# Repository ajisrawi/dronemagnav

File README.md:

# DroneMagNav — magnetic-anomaly navigation board for drones

GNSS-denied positioning from the Earth's crustal magnetic field, plus a
phone-operated great-circle route planner.

```
  LIS3MDL magnetometer ─┐                          ┌─ WDMAM anomaly map (SD)
  BMI088 IMU ───────────┼─ ESP32-S3 ─ particle ────┤  WMM core field model
  BMP280 baro ──────────┘   filter    matching     └─ Tolles-Lawson compensation
        │                        │
   u-blox GNSS (init/truth)      ├─ MAVLink GPS_INPUT → flight controller
                                 └─ WiFi AP → phone: offline map, route, upload
```

## Deliverables

| Item | Where | Status |
|---|---|---|
| Schematics (5 sheets) | `hardware/dronemagnav/*.kicad_sch`, `dronemagnav-schematic.pdf` | ERC 0 errors (1 intended warning) |
| PCB 64 × 60 mm, 4-layer, 30.5 mm Pixhawk hole pattern | `hardware/dronemagnav/dronemagnav.kicad_pcb` | routed, 0 unconnected, 0 electrical DRC |
| Fab package | `hardware/dronemagnav/fab/` (Gerber ZIP, drill, pick-and-place) | ready to upload |
| BOM | `docs/BOM.csv` | 28 line items, 56 parts, MPNs |
| Firmware (ESP32-S3, PlatformIO) | `firmware/`, images in `firmware/release/` | compiles with 0 warnings (Arduino-ESP32 3.3.11); WMM core-field model validated 100/100 against NOAA test vectors (0.001 nT) |
| Phone UI | `firmware/sdcard/www/index.html` | offline map, tap-to-route, upload |
| SD-card preparation | `tools/prepare_sd.py` | WDMAM v2 (1.5 GB text) → 51.9 MB binary grid, verified by `tools/wdmam_check.py`; WMM, coastline |
| Design document | `DroneMagNav-Design-Document.pdf` | study, diagrams, PCB, BOM, verification |

## Hardware
| Block | Part | Why |
|---|---|---|
| MCU / radio | ESP32-S3-WROOM-1-N16R8 | WiFi AP for the phone page, BLE, native USB, 8 MB PSRAM for map tiles + particle filter |
| Magnetometer | LIS3MDL (SPI) | 16-bit, ~40 nT after averaging; RM3100 upgrade via mast connector J5 |
| IMU | BMI088 (SPI) | drone-grade accel + gyro, vibration-robust |
| Barometer | BMP280 (SPI) | altitude for the field model |
| GNSS | u-blox MAX-M10S + U.FL | initialisation and truth reference |
| Storage | microSD (SDMMC 4-bit) | world anomaly map, WMM, coastline, web page |
| Interfaces | USB-C, JST-GH TELEM (MAVLink, 5 V in), JST-GH sensor mast (I2C) | Pixhawk-standard |
| Power | USB/FC 5 V → AMS1117-3.3 (digital) + AP2112K-3.3 (sensors) | separate clean sensor rail |

## How it navigates
1. **Compensate** the scalar field for the drone's own magnetism (18-term
   Tolles-Lawson, fitted once in flight with GNSS).
2. **Predict** position with the flight controller's velocity (or IMU dead
   reckoning) in a 600-particle filter.
3. **Update** each particle against *WMM core field + WDMAM anomaly* at the
   particle's location; resample; output mean and 1-σ.
4. **Feed** the estimate to the autopilot as `GPS_INPUT` when GNSS is lost.

**Expectations, honestly:** the WDMAM world grid is 3 arc-min (~5 km) and
upward-continued to 5 km, so with it alone you get drift-free
*kilometre-class* positioning — right for oceanic/jammed cruise, not landing.
Load a local aeromagnetic survey (`/maps/local.bin`, same format) for tens of
metres at drone altitude.

## Routing
The phone page shows an offline world coastline, you tap START and DEST, the
board computes the **great-circle** (shortest) path as evenly spaced waypoints
and uploads them to the flight controller as a MAVLink mission.

## Build / flash / prepare
See `firmware/README.md`. Short version: `pio run -t upload` over USB-C, then
`python tools/prepare_sd.py --wdmam <file> --wmm WMM.COF --coast <geojson>`
and copy `firmware/sdcard/*` to the card.

## Status / caveats
- Prototype; not certified for any regulated use.
- Firmware builds cleanly (PlatformIO, pioarduino platform, Arduino-ESP32
  core 3.3.11: 0 warnings, 1.08 MB flash of 4 MB app partition, 94 KB RAM).
  Ready-to-flash images are in `firmware/release/`. It has not yet run on
  real hardware, since the board has not been built.
- Vias in pads: 74 power vias were moved out of their pads into dog-bone
  stubs. Three remain where the routing leaves no room (BMI088 pads 2 and 4,
  microSD VDD pad) and must be filled and capped, see
  `hardware/dronemagnav/fab/FABRICATION-NOTES.md` (included in the Gerber ZIP).
- MAX-M10S straps checked against the u-blox integration manual
  (UBX-20053088 R05): `VIO_SEL` left open selects 3.3 V I/O, which is what the
  board supplies, so no change was needed. TIMEPULSE is tied inside the module
  to SAFEBOOT_N, so the firmware keeps GPIO16 input-only.
- Map data: WDMAM from the link you supplied; WMM.COF (NOAA) and Natural Earth
  coastline are free downloads you run through `prepare_sd.py`.

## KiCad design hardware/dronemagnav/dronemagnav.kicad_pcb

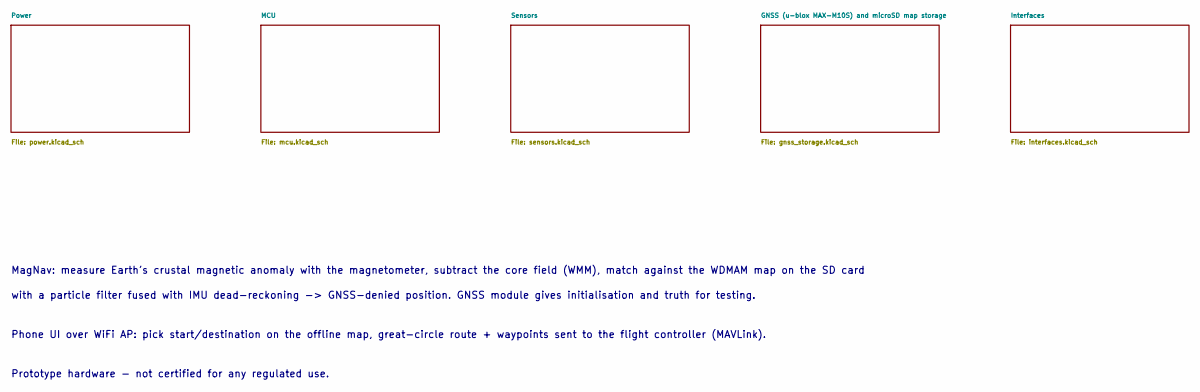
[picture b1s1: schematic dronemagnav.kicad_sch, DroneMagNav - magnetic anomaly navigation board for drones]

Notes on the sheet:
MagNav: measure Earth's crustal magnetic anomaly with the magnetometer, subtract the core field (WMM), match against the WDMAM map on the SD card
with a particle filter fused with IMU dead-reckoning -> GNSS-denied position. GNSS module gives initialisation and truth for testing.
Phone UI over WiFi AP: pick start/destination on the offline map, great-circle route + waypoints sent to the flight controller (MAVLink).
Prototype hardware - not certified for any regulated use.

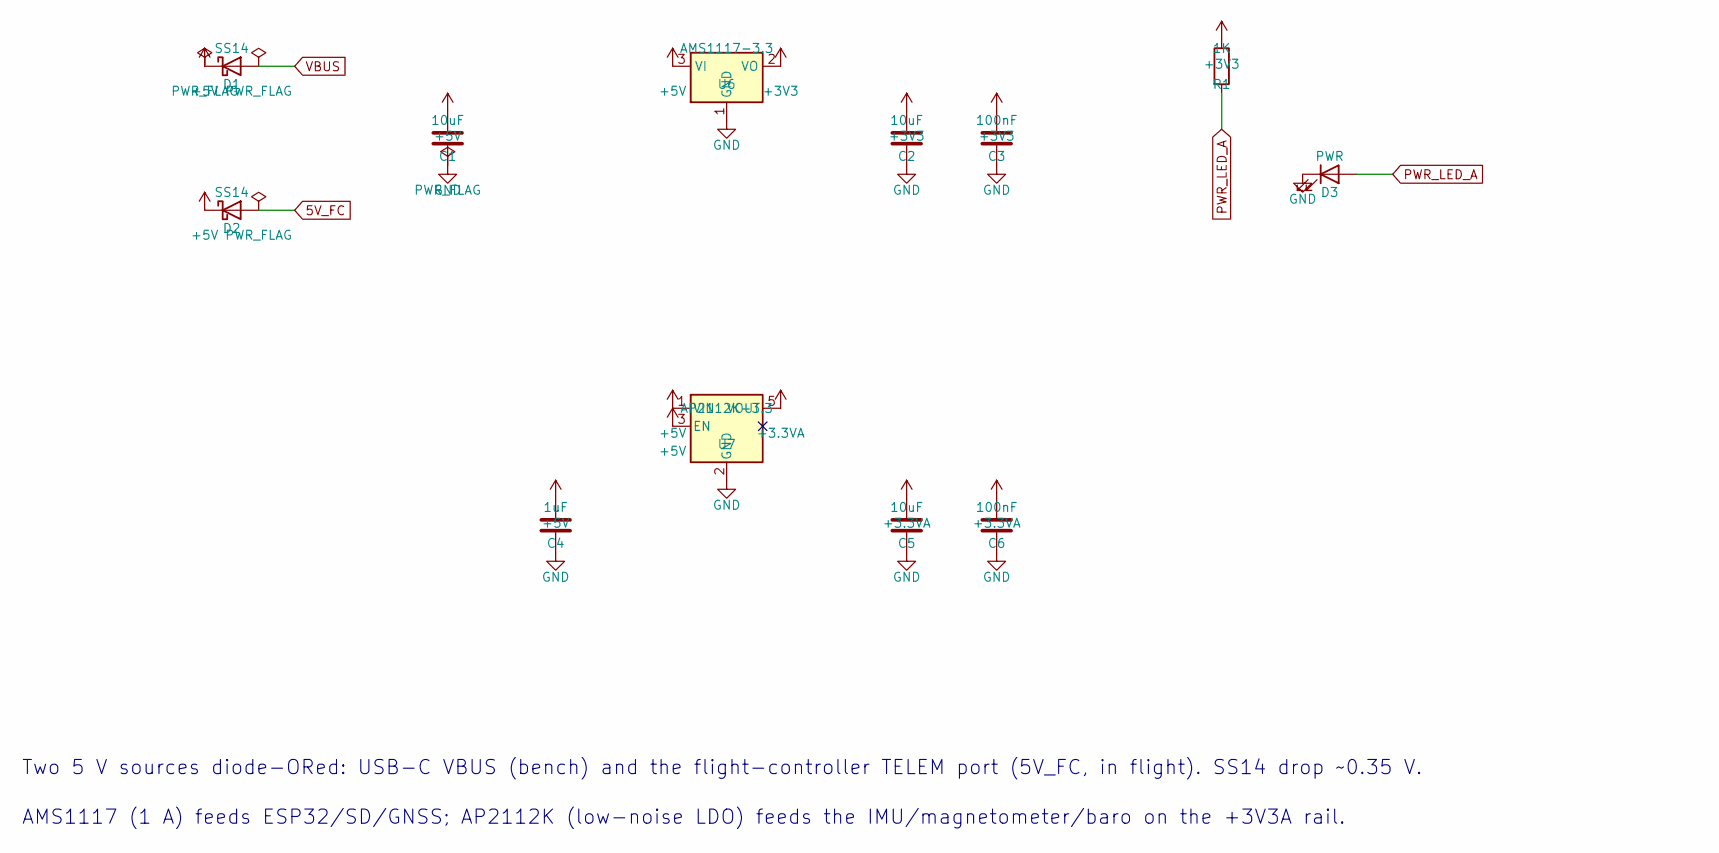
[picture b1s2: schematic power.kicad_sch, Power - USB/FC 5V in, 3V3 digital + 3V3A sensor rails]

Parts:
C1, C2, C5: 10uF; C_0805_2012Metric
C3, C6: 100nF; C_0603_1608Metric
C4: 1uF; C_0603_1608Metric
D1, D2: SS14; D_SMA
D3: PWR; LED_0603_1608Metric
R1: 1K; R_0603_1608Metric
U6: AMS1117-3.3; SOT-223-3_TabPin2
U7: AP2112K-3.3; SOT-23-5

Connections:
+3.3VA: C5.1, C6.1, U7.5 (VOUT); also elsewhere on the board
+3V3: C2.1, C3.1, R1.1, U6.2 (VO); also elsewhere on the board
PWR_LED_A: D3.2 (A), R1.2

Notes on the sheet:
Two 5 V sources diode-ORed: USB-C VBUS (bench) and the flight-controller TELEM port (5V_FC, in flight). SS14 drop ~0.35 V.
AMS1117 (1 A) feeds ESP32/SD/GNSS; AP2112K (low-noise LDO) feeds the IMU/magnetometer/baro on the +3V3A rail.

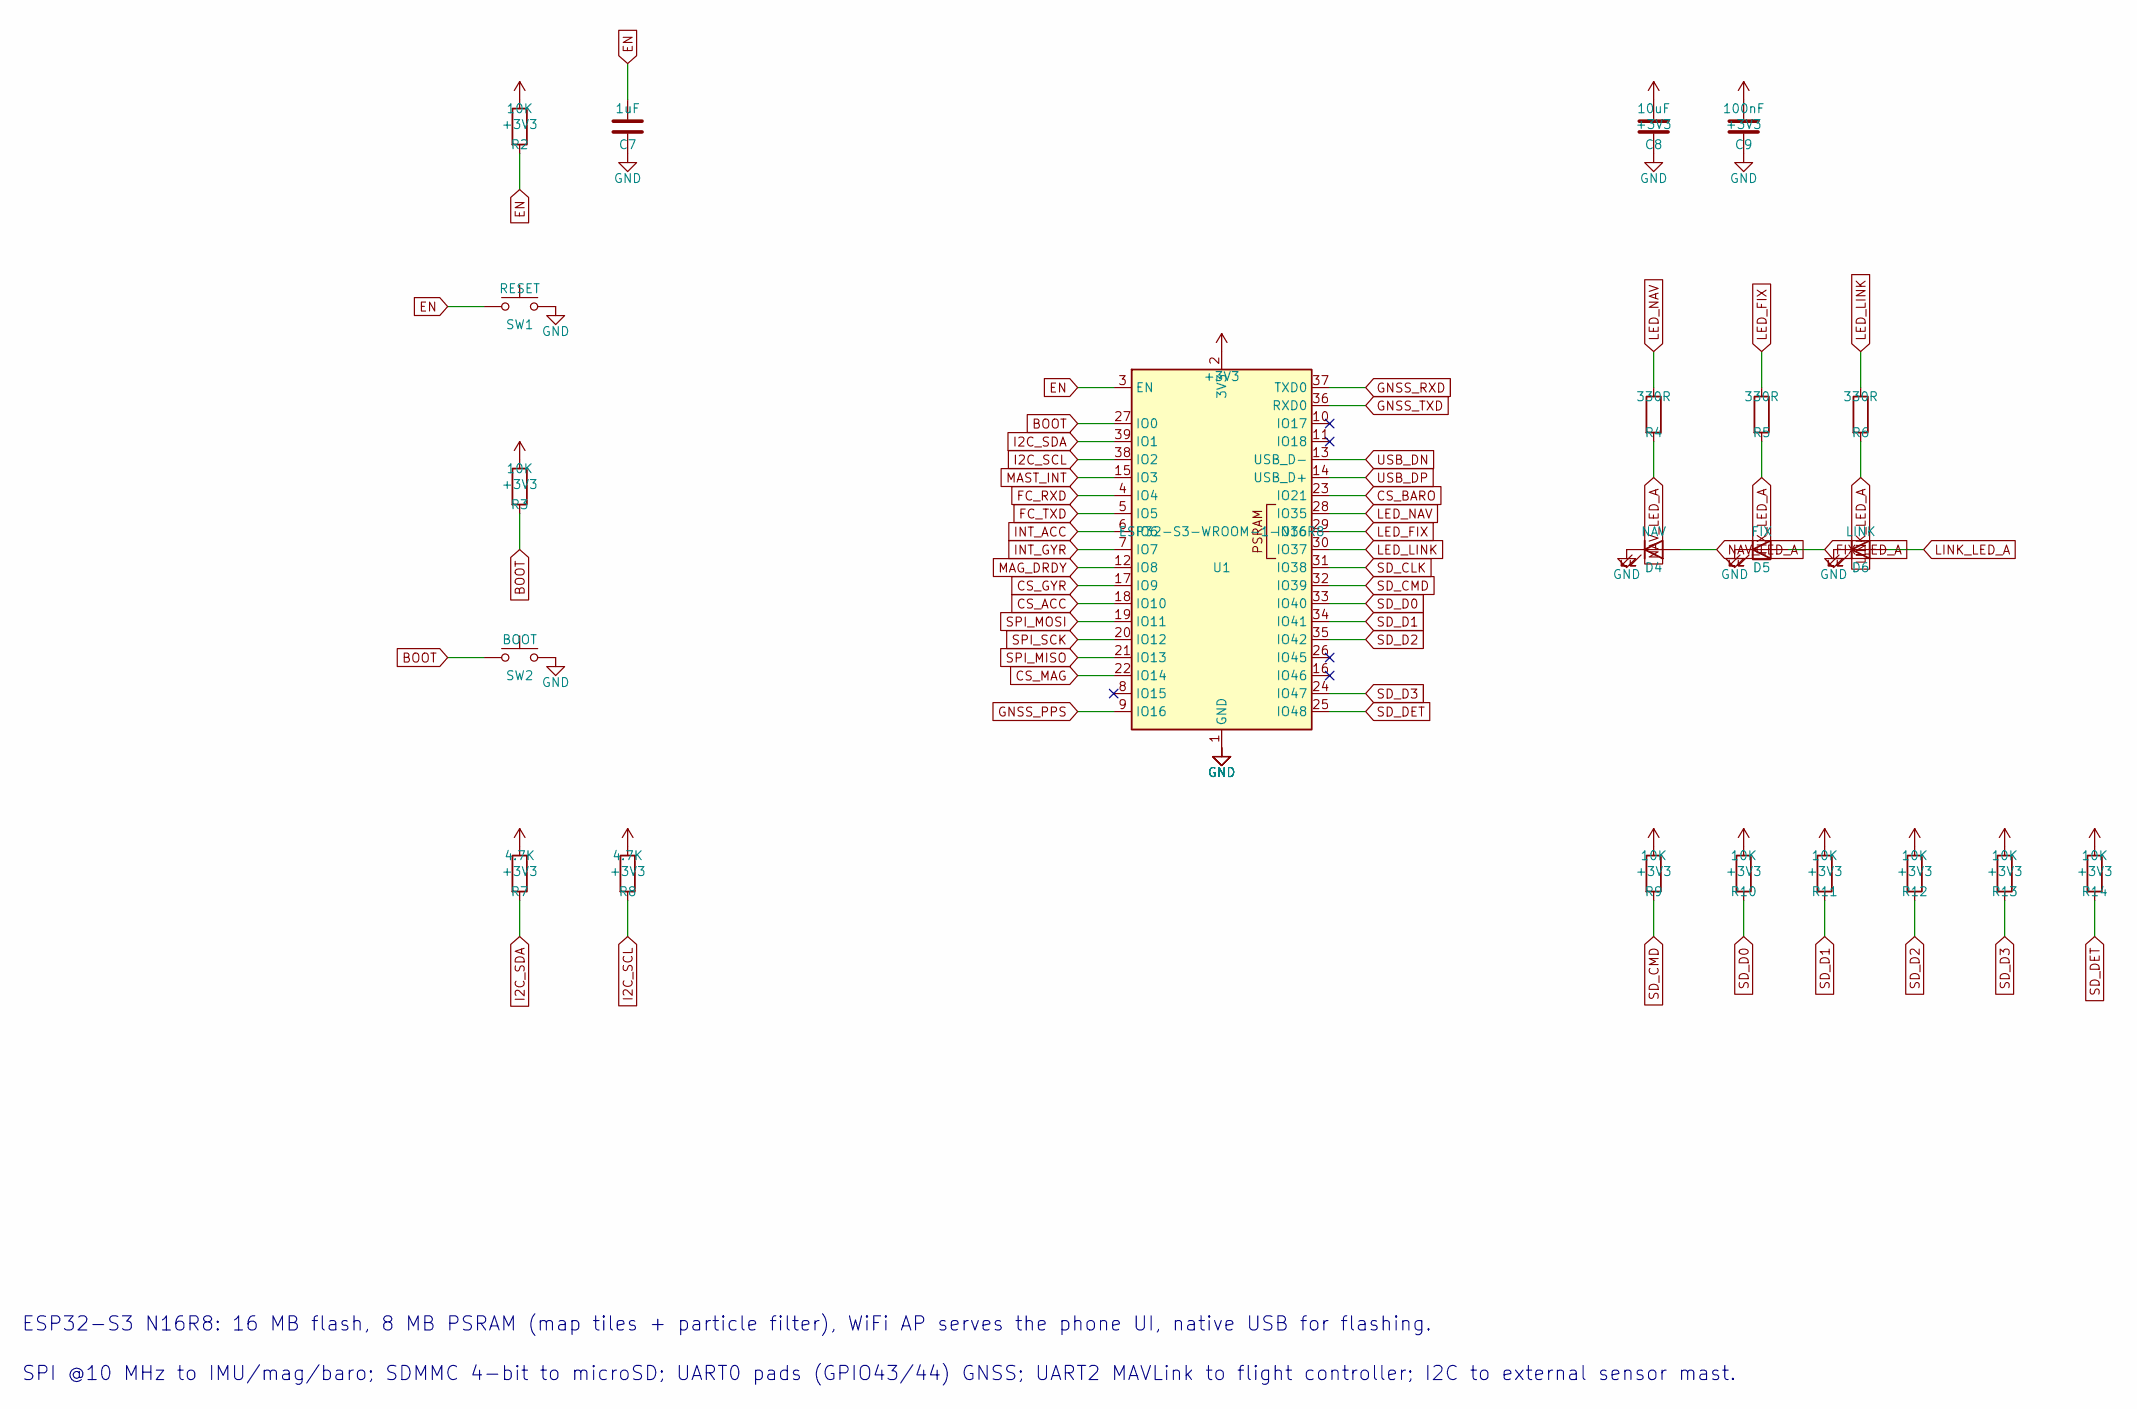
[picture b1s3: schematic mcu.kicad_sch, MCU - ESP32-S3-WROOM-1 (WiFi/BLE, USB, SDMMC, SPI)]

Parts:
C7: 1uF; C_0603_1608Metric
C8: 10uF; C_0805_2012Metric
C9: 100nF; C_0603_1608Metric
D4: NAV; LED_0603_1608Metric
D5: FIX; LED_0603_1608Metric
D6: LINK; LED_0603_1608Metric
R2, R3, R9, R10, R11, R12, R13, R14: 10K; R_0603_1608Metric
R4, R5, R6: 330R; R_0603_1608Metric
R7, R8: 4.7K; R_0603_1608Metric
SW1: RESET; SW_SPST_PTS645Sx43SMTR92
SW2: BOOT; SW_SPST_PTS645Sx43SMTR92
U1: ESP32-S3-WROOM-1-N16R8; ESP32-S3-WROOM-1

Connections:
+3V3: C8.1, C9.1, R2.1, R3.1, R7.1, R8.1, R9.1, R10.1, R11.1, R12.1, R13.1, R14.1, U1.2 (3V3); also elsewhere on the board
BOOT: R3.2, SW2.1, U1.27 (IO0)
CS_ACC: U1.18 (IO10); also elsewhere on the board
CS_BARO: U1.23 (IO21); also elsewhere on the board
CS_GYR: U1.17 (IO9); also elsewhere on the board
CS_MAG: U1.22 (IO14); also elsewhere on the board
EN: C7.1, R2.2, SW1.1, U1.3 (EN)
FC_RXD: U1.4 (IO4); also elsewhere on the board
FC_TXD: U1.5 (IO5); also elsewhere on the board
FIX_LED_A: D5.2 (A), R5.2
GNSS_PPS: U1.9 (IO16); also elsewhere on the board
GNSS_RXD: U1.37 (TXD0); also elsewhere on the board
GNSS_TXD: U1.36 (RXD0); also elsewhere on the board
I2C_SCL: R8.2, U1.38 (IO2); also elsewhere on the board
I2C_SDA: R7.2, U1.39 (IO1); also elsewhere on the board
INT_ACC: U1.6 (IO6); also elsewhere on the board
INT_GYR: U1.7 (IO7); also elsewhere on the board
LED_FIX: R5.1, U1.29 (IO36)
LED_LINK: R6.1, U1.30 (IO37)
LED_NAV: R4.1, U1.28 (IO35)
LINK_LED_A: D6.2 (A), R6.2
MAG_DRDY: U1.12 (IO8); also elsewhere on the board
MAST_INT: U1.15 (IO3); also elsewhere on the board
NAV_LED_A: D4.2 (A), R4.2
SD_CLK: U1.31 (IO38); also elsewhere on the board
SD_CMD: R9.2, U1.32 (IO39); also elsewhere on the board
SD_D0: R10.2, U1.33 (IO40); also elsewhere on the board
SD_D1: R11.2, U1.34 (IO41); also elsewhere on the board
SD_D2: R12.2, U1.35 (IO42); also elsewhere on the board
SD_D3: R13.2, U1.24 (IO47); also elsewhere on the board
SD_DET: R14.2, U1.25 (IO48); also elsewhere on the board
SPI_MISO: U1.21 (IO13); also elsewhere on the board
SPI_MOSI: U1.19 (IO11); also elsewhere on the board
SPI_SCK: U1.20 (IO12); also elsewhere on the board
USB_DN: U1.13 (USB_D-); also elsewhere on the board
USB_DP: U1.14 (USB_D+); also elsewhere on the board

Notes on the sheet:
ESP32-S3 N16R8: 16 MB flash, 8 MB PSRAM (map tiles + particle filter), WiFi AP serves the phone UI, native USB for flashing.
SPI @10 MHz to IMU/mag/baro; SDMMC 4-bit to microSD; UART0 pads (GPIO43/44) GNSS; UART2 MAVLink to flight controller; I2C to external sensor mast.

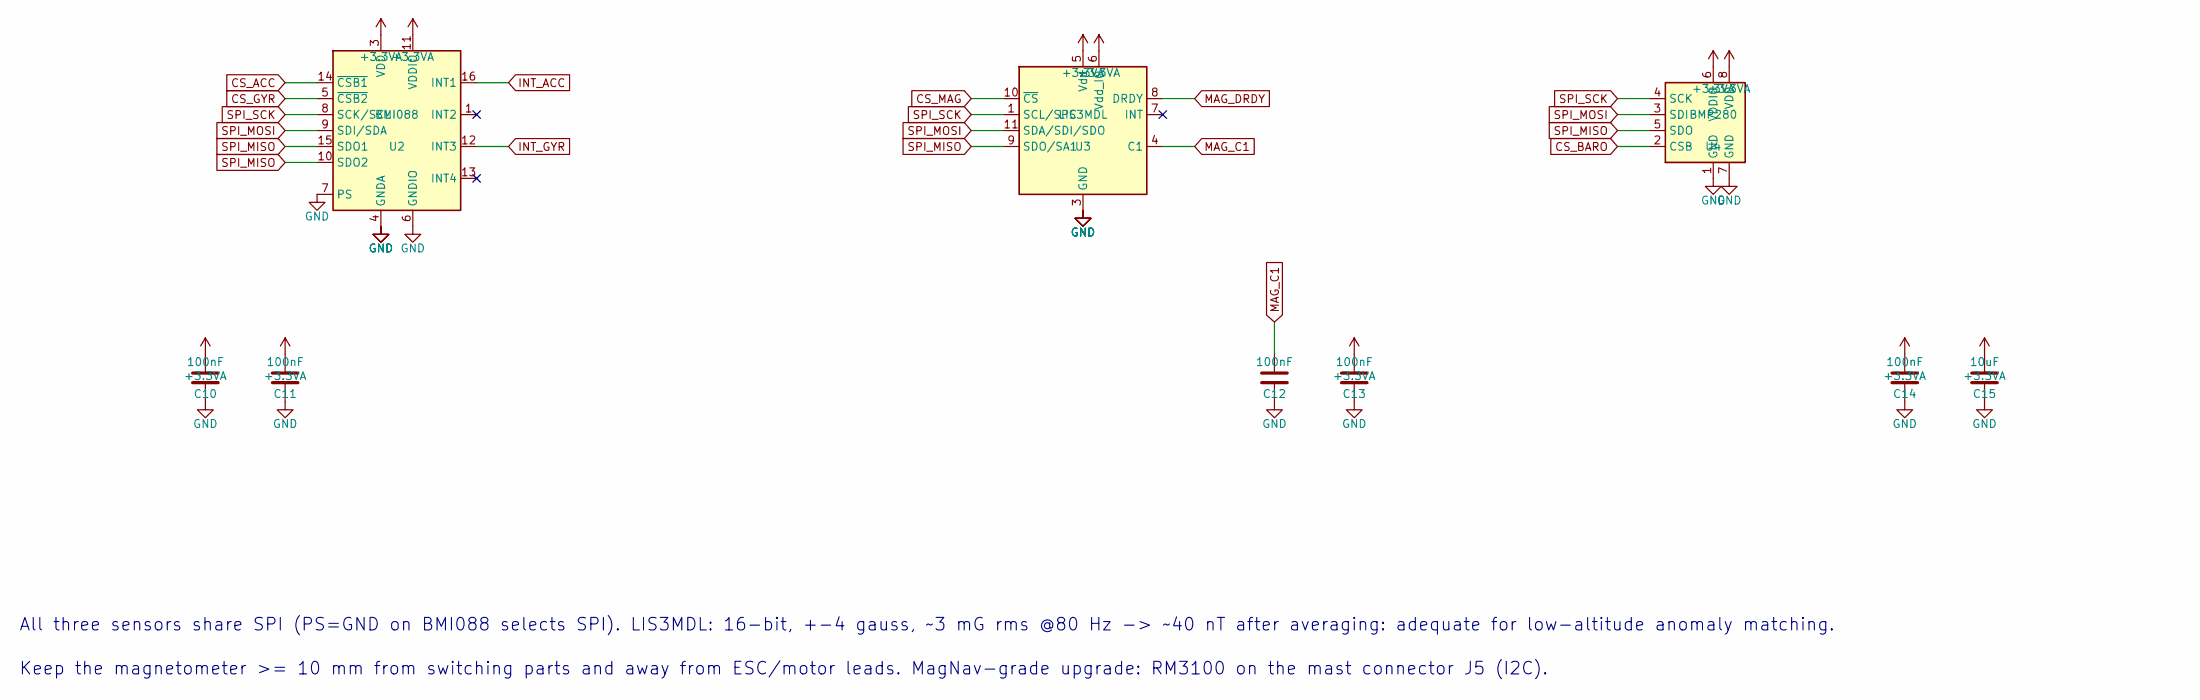
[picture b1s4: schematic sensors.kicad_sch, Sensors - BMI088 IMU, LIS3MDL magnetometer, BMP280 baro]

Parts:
C10, C11, C12, C13, C14: 100nF; C_0603_1608Metric
C15: 10uF; C_0805_2012Metric
U2: BMI088; Bosch_LGA-16_4.5x3mm_P0.5mm_LayoutBorder7x1y_ClockwisePinNu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
U3: LIS3MDL; LGA-12_2x2mm_P0.5mm
U4: BMP280; Bosch_LGA-8_2x2.5mm_P0.65mm_ClockwisePinNumbering

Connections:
+3.3VA: C10.1, C11.1, C13.1, C14.1, C15.1, U2.3 (VDD), U2.11 (VDDIO), U3.5 (Vdd), U3.6 (Vdd_IO), U4.6 (VDDIO), U4.8 (VDD); also elsewhere on the board
CS_ACC: U2.14 (~CSB1); also elsewhere on the board
CS_BARO: U4.2 (CSB); also elsewhere on the board
CS_GYR: U2.5 (~CSB2); also elsewhere on the board
CS_MAG: U3.10 (~CS); also elsewhere on the board
INT_ACC: U2.16 (INT1); also elsewhere on the board
INT_GYR: U2.12 (INT3); also elsewhere on the board
MAG_C1: C12.1, U3.4 (C1)
MAG_DRDY: U3.8 (DRDY); also elsewhere on the board
SPI_MISO: U2.10 (SDO2), U2.15 (SDO1), U3.9 (SDO/SA1), U4.5 (SDO); also elsewhere on the board
SPI_MOSI: U2.9 (SDI/SDA), U3.11 (SDA/SDI/SDO), U4.3 (SDI); also elsewhere on the board
SPI_SCK: U2.8 (SCK/SCL), U3.1 (SCL/SPC), U4.4 (SCK); also elsewhere on the board

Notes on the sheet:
All three sensors share SPI (PS=GND on BMI088 selects SPI). LIS3MDL: 16-bit, +-4 gauss, ~3 mG rms @80 Hz -> ~40 nT after averaging: adequate for low-altitude anomaly matching.
Keep the magnetometer >= 10 mm from switching parts and away from ESC/motor leads. MagNav-grade upgrade: RM3100 on the mast connector J5 (I2C).

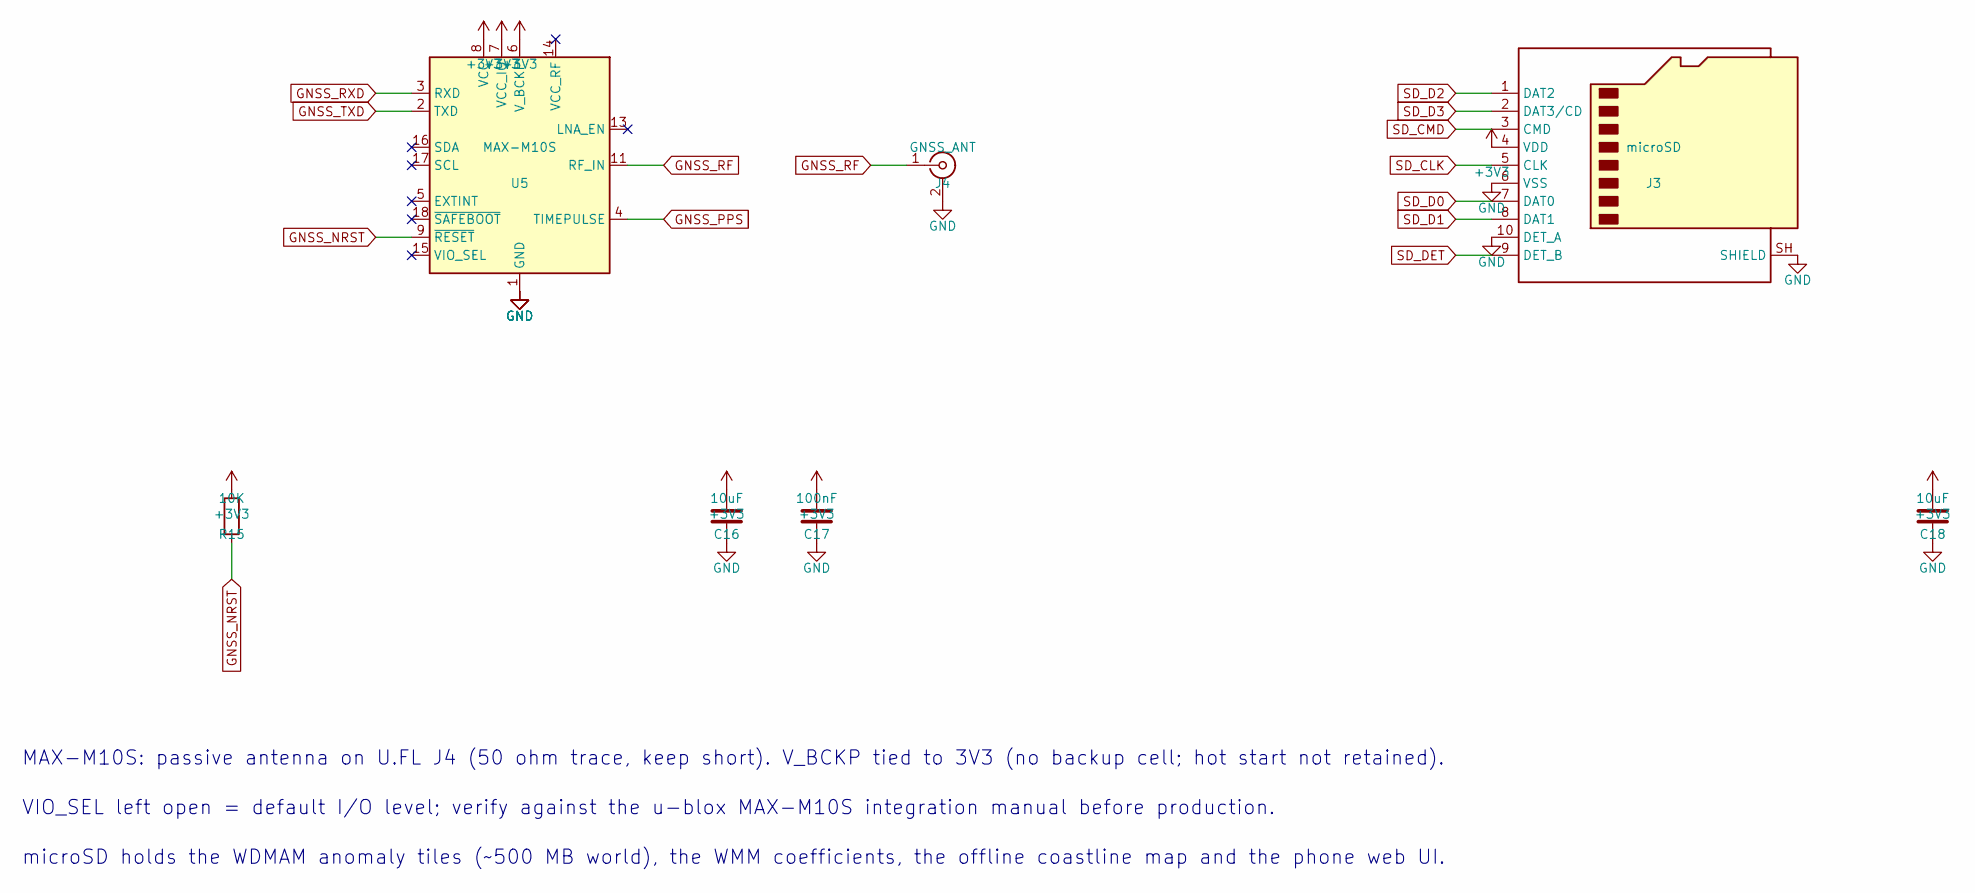
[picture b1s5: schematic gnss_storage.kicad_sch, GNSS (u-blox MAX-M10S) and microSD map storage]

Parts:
C16, C18: 10uF; C_0805_2012Metric
C17: 100nF; C_0603_1608Metric
J3: microSD; microSD_HC_Hirose_DM3AT-SF-PEJM5
J4: GNSS_ANT; U.FL_Hirose_U.FL-R-SMT-1_Vertical
R15: 10K; R_0603_1608Metric
U5: MAX-M10S; ublox_MAX

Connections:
+3V3: C16.1, C17.1, C18.1, J3.4 (VDD), R15.1, U5.6 (V_BCKP), U5.7 (VCC_IO), U5.8 (VCC); also elsewhere on the board
GNSS_NRST: R15.2, U5.9 (~RESET)
GNSS_PPS: U5.4 (TIMEPULSE); also elsewhere on the board
GNSS_RF: J4.1 (In), U5.11 (RF_IN)
GNSS_RXD: U5.3 (RXD); also elsewhere on the board
GNSS_TXD: U5.2 (TXD); also elsewhere on the board
SD_CLK: J3.5 (CLK); also elsewhere on the board
SD_CMD: J3.3 (CMD); also elsewhere on the board
SD_D0: J3.7 (DAT0); also elsewhere on the board
SD_D1: J3.8 (DAT1); also elsewhere on the board
SD_D2: J3.1 (DAT2); also elsewhere on the board
SD_D3: J3.2 (DAT3/CD); also elsewhere on the board
SD_DET: J3.9 (DET_B); also elsewhere on the board

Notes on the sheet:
MAX-M10S: passive antenna on U.FL J4 (50 ohm trace, keep short). V_BCKP tied to 3V3 (no backup cell; hot start not retained).
VIO_SEL left open = default I/O level; verify against the u-blox MAX-M10S integration manual before production.
microSD holds the WDMAM anomaly tiles (~500 MB world), the WMM coefficients, the offline coastline map and the phone web UI.

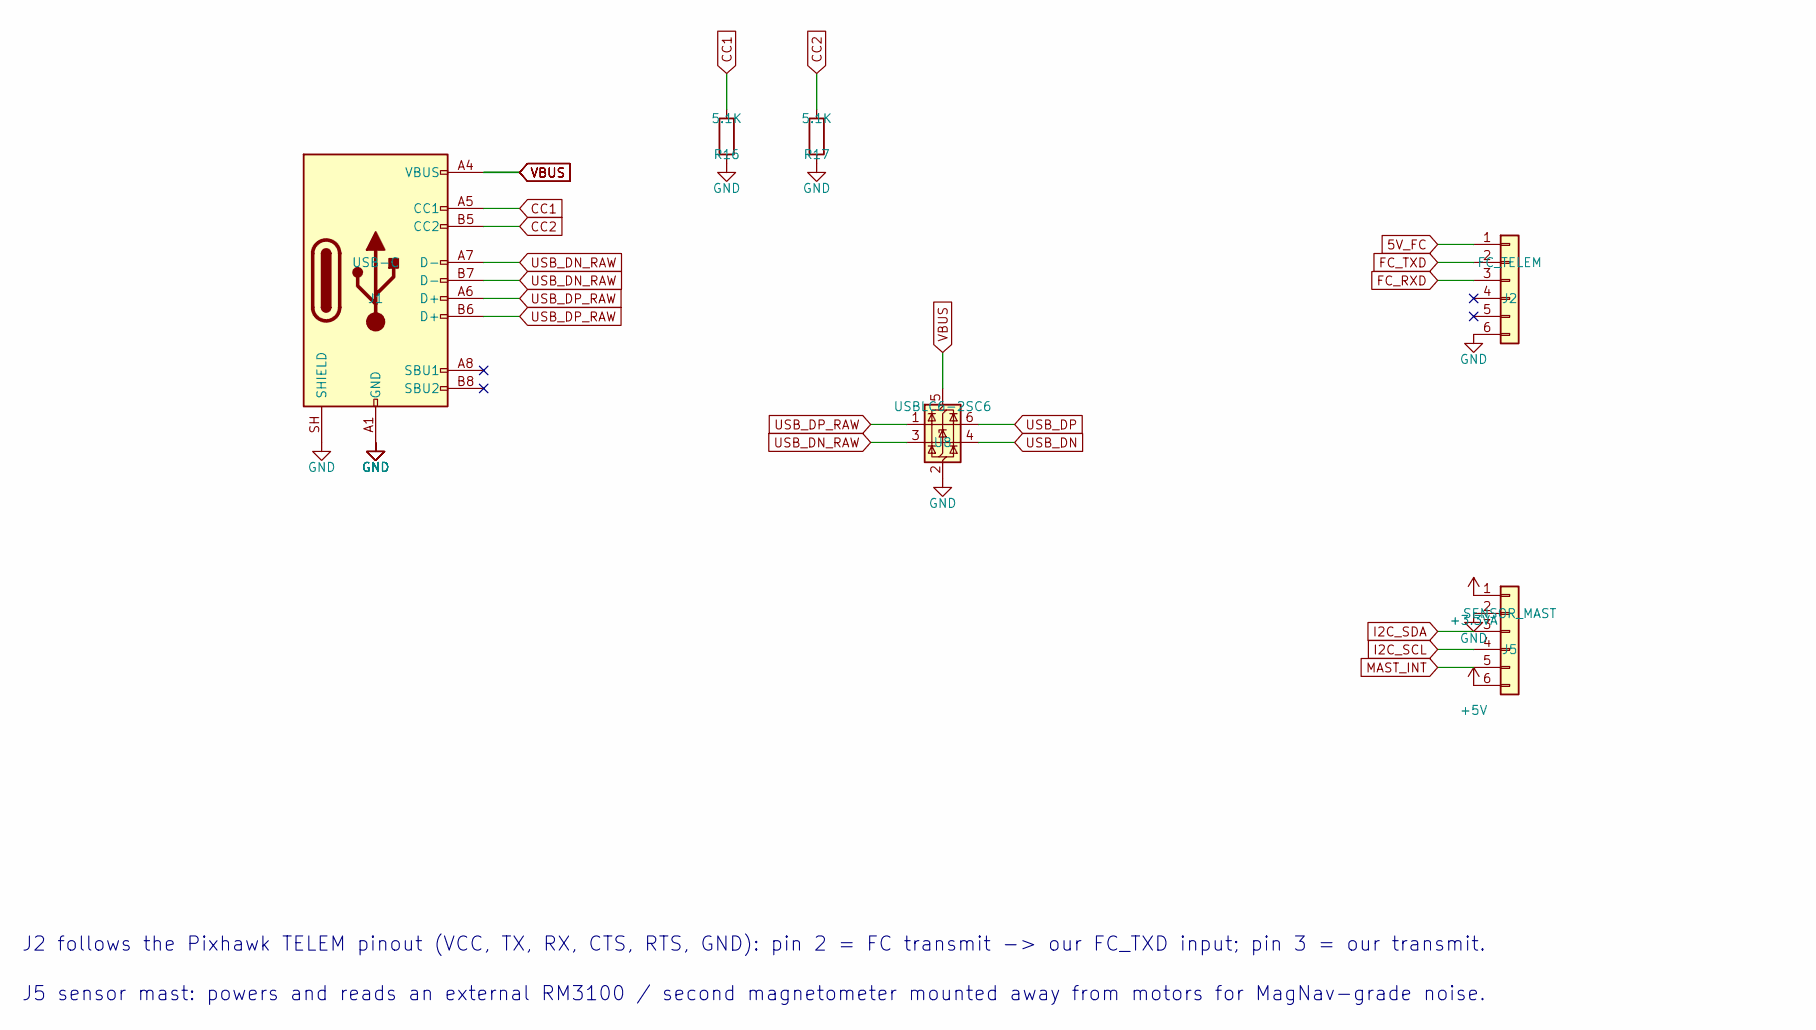
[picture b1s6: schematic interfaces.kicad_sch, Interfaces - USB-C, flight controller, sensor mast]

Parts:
J1: USB-C; USB_C_Receptacle_HRO_TYPE-C-31-M-12
J2: FC_TELEM; JST_GH_SM06B-GHS-TB_1x06-1MP_P1.25mm_Horizontal
J5: SENSOR_MAST; JST_GH_SM06B-GHS-TB_1x06-1MP_P1.25mm_Horizontal
R16, R17: 5.1K; R_0603_1608Metric
U8: USBLC6-2SC6; SOT-23-6

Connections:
+3.3VA: J5.1; also elsewhere on the board
CC1: J1.A5 (CC1), R16.1
CC2: J1.B5 (CC2), R17.1
FC_RXD: J2.3; also elsewhere on the board
FC_TXD: J2.2; also elsewhere on the board
I2C_SCL: J5.4; also elsewhere on the board
I2C_SDA: J5.3; also elsewhere on the board
MAST_INT: J5.5; also elsewhere on the board
USB_DN: U8.4 (I/O2); also elsewhere on the board
USB_DN_RAW: J1.A7 (D-), J1.B7 (D-), U8.3 (I/O2)
USB_DP: U8.6 (I/O1); also elsewhere on the board
USB_DP_RAW: J1.A6 (D+), J1.B6 (D+), U8.1 (I/O1)

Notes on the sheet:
J2 follows the Pixhawk TELEM pinout (VCC, TX, RX, CTS, RTS, GND): pin 2 = FC transmit -> our FC_TXD input; pin 3 = our transmit.
J5 sensor mast: powers and reads an external RM3100 / second magnetometer mounted away from motors for MagNav-grade noise.

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
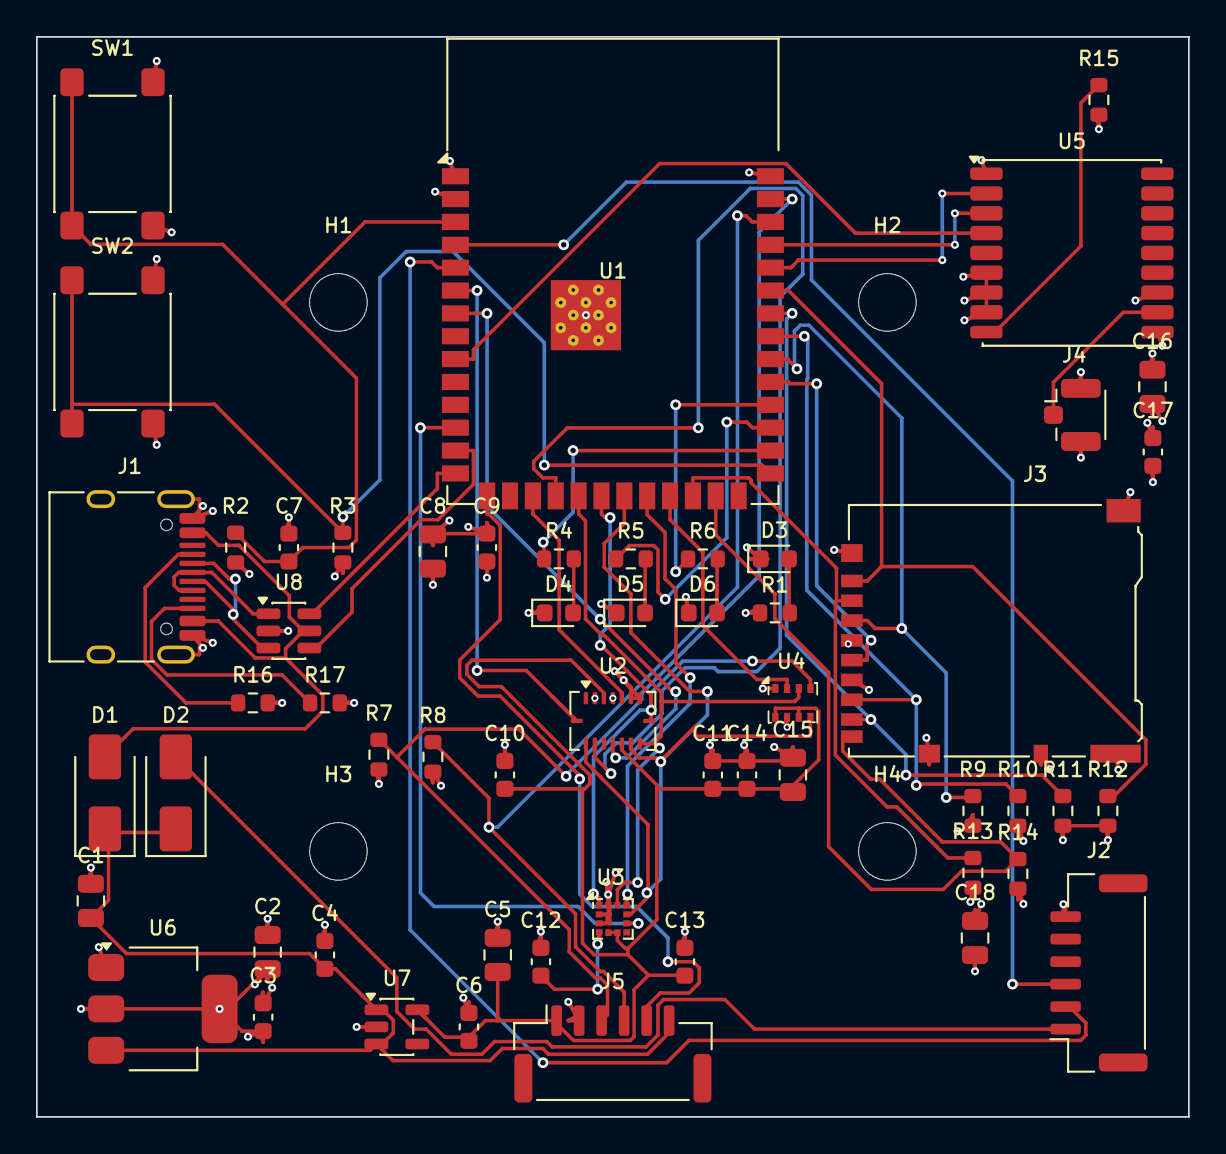
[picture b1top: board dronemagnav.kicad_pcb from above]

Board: 4 copper layers, 64.0 x 60.0 mm, 60 parts (0 on the bottom side), 49 nets.

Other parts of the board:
H1, H2, H3, H4: M3; MountingHole_3.2mm_M3

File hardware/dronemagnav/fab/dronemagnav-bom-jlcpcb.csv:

Comment,Designator,Footprint,Quantity,LCSC Part #,Manufacturer,MPN
10uF,"C1,C2,C5,C8,C15,C16,C18",C_0805_2012Metric,7,C15850,Samsung,CL21 series
100nF,"C3,C6,C9,C10,C11,C12,C13,C14,C17",C_0603_1608Metric,9,C14663,Samsung,CL10 series
1uF,"C4,C7",C_0603_1608Metric,2,C15849,Samsung,CL10 series
SS14,"D1,D2",D_SMA,2,C2480,Vishay / MDD,SS14
LED green 0603,D3,LED_0603_1608Metric,1,,Everlight,19-217/GHC-YR1S2/3T
LED green 0603,D4,LED_0603_1608Metric,1,,Everlight,19-217/GHC-YR1S2/3T
LED blue 0603,D5,LED_0603_1608Metric,1,,Everlight,19-217/BHC-ZL1M2RY/3T
LED yellow 0603,D6,LED_0603_1608Metric,1,,Everlight,19-217/Y2C-CQ2R2L/3T
"USB-C receptacle, USB 2.0, 16-pin",J1,USB_C_Receptacle_HRO_TYPE-C-31-M-12,1,C165948,HRO,TYPE-C-31-M-12
"JST-GH 6-pin, Pixhawk TELEM pinout",J2,JST_GH_SM06B-GHS-TB_1x06-1MP_P1.25mm_Horizontal,1,,JST,SM06B-GHS-TB
"microSD card socket, push-push",J3,microSD_HC_Hirose_DM3AT-SF-PEJM5,1,,Hirose,DM3AT-SF-PEJM5
U.FL RF connector for GNSS antenna,J4,U.FL_Hirose_U.FL-R-SMT-1_Vertical,1,,Hirose,U.FL-R-SMT-1(10)
"JST-GH 6-pin, external sensor mast",J5,JST_GH_SM06B-GHS-TB_1x06-1MP_P1.25mm_Horizontal,1,,JST,SM06B-GHS-TB
1K,R1,R_0603_1608Metric,1,C21190,Yageo,RC0603FR-071KL
10K,"R2,R3,R9,R10,R11,R12,R13,R14,R15",R_0603_1608Metric,9,C25804,Yageo,RC0603FR-0710KL
330R,"R4,R5,R6",R_0603_1608Metric,3,C23138,Yageo,RC0603FR-07330RL
4.7K,"R7,R8",R_0603_1608Metric,2,C23162,Yageo,RC0603FR-074.7KL
5.1K,"R16,R17",R_0603_1608Metric,2,C23186,Yageo,RC0603FR-075.1KL
Tactile switch 6x6 SMD,SW1,SW_SPST_PTS645Sx43SMTR92,1,,C&K,PTS645SM43SMTR92
Tactile switch 6x6 SMD,SW2,SW_SPST_PTS645Sx43SMTR92,1,,C&K,PTS645SM43SMTR92
ESP32-S3-WROOM-1-N16R8,U1,ESP32-S3-WROOM-1,1,C2913202,Espressif,ESP32-S3-WROOM-1-N16R8
BMI088,U2,Bosch_LGA-16_4.5x3mm_P0.5mm_LayoutBorder7x1y_ClockwisePinNumbering,1,C194919,Bosch,BMI088
LIS3MDL,U3,LGA-12_2x2mm_P0.5mm,1,C478483,STMicroelectronics,LIS3MDLTR
BMP280,U4,Bosch_LGA-8_2x2.5mm_P0.65mm_ClockwisePinNumbering,1,C83291,Bosch,BMP280
MAX-M10S,U5,ublox_MAX,1,C5291404,u-blox,MAX-M10S-00B
AMS1117-3.3,U6,SOT-223-3_TabPin2,1,C6186,AMS / UMW,AMS1117-3.3
AP2112K-3.3,U7,SOT-23-5,1,C22365427,Diodes Inc.,AP2112K-3.3TRG1
USBLC6-2SC6,U8,SOT-23-6,1,C2687116,STMicroelectronics,USBLC6-2SC6

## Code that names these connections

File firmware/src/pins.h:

// DroneMagNav board pin map - matches schematic rev A (hardware/dronemagnav)
#pragma once

// SPI sensor bus (BMI088 accel/gyro, LIS3MDL magnetometer, BMP280 baro)
#define PIN_SPI_SCK    12
#define PIN_SPI_MOSI   11
#define PIN_SPI_MISO   13
#define PIN_CS_ACC     10
#define PIN_CS_GYR      9
#define PIN_CS_MAG     14
#define PIN_CS_BARO    21
#define PIN_INT_ACC     6
#define PIN_INT_GYR     7
#define PIN_MAG_DRDY    8

// GNSS (u-blox MAX-M10S) on the UART0 pads (GPIO43 TXD0 / GPIO44 RXD0);
// the console is the native USB-CDC port, so UART0 is free
#define PIN_GNSS_TX    43   // ESP TXD0 -> GNSS RXD
#define PIN_GNSS_RX    44   // GNSS TXD -> ESP RXD0
#define PIN_GNSS_PPS   16

// Flight controller MAVLink on UART2 (JST-GH TELEM pinout)
#define PIN_FC_TX       4   // ESP -> FC RX
#define PIN_FC_RX       5   // FC TX -> ESP

// I2C sensor-mast connector (external RM3100 etc.)
#define PIN_I2C_SDA     1
#define PIN_I2C_SCL     2
#define PIN_MAST_INT    3

// microSD, SDMMC 4-bit
#define PIN_SD_CLK     38
#define PIN_SD_CMD     39
#define PIN_SD_D0      40
#define PIN_SD_D1      41
#define PIN_SD_D2      42
#define PIN_SD_D3      47
#define PIN_SD_DET     48   // low = card present

// status LEDs
#define PIN_LED_NAV    35
#define PIN_LED_FIX    36
#define PIN_LED_LINK   37
